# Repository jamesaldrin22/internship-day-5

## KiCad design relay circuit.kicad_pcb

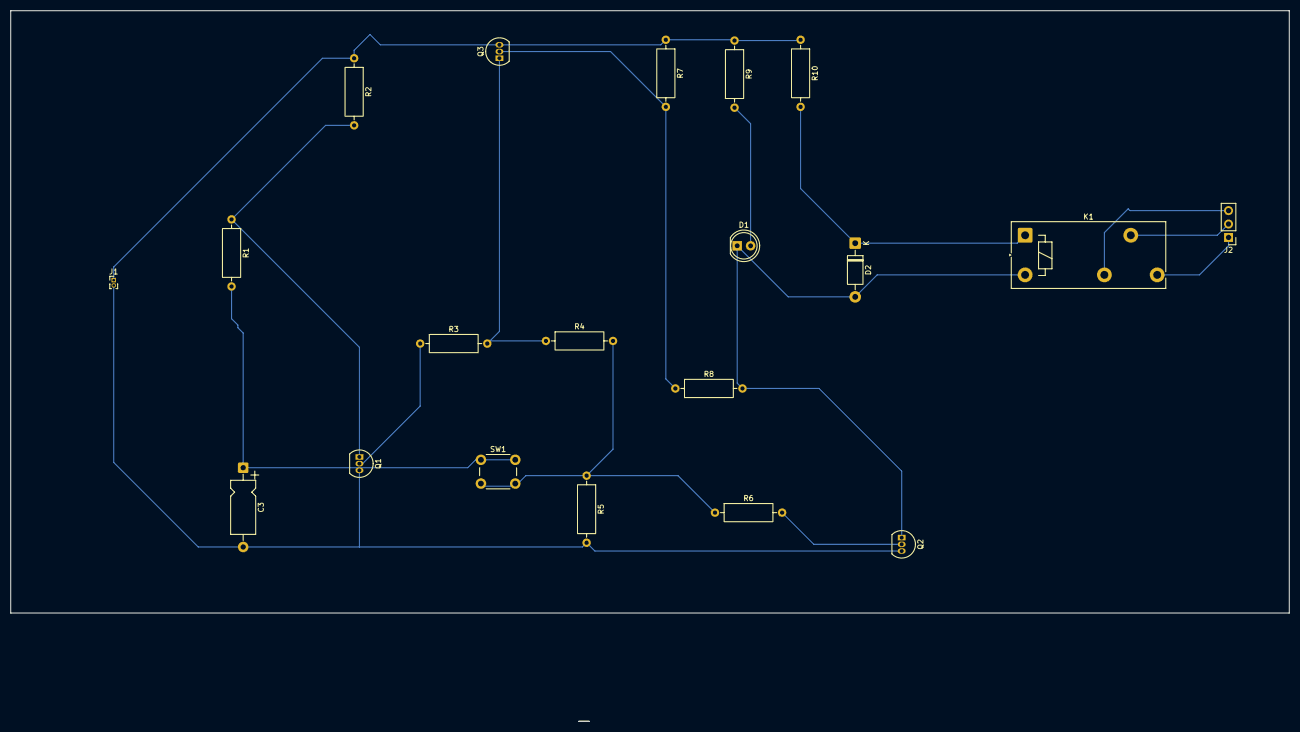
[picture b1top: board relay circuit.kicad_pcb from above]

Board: 2 copper layers, 242.0 x 114.0 mm, 20 parts (0 on the bottom side), 15 nets.

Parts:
C3: C_Polarized_US; CP_Axial_L10.0mm_D4.5mm_P15.00mm_Horizontal
D1: LED; LED_D5.0mm
D2: 1N4007; D_DO-41_SOD81_P10.16mm_Horizontal
J1: Conn_01x02_Pin; PinHeader_1x02_P1.00mm_Vertical
J2: Conn_01x03_Pin; PinHeader_1x03_P2.54mm_Vertical
K1: Fujitsu_FTR-LYCA005x; Relay_SPDT_Finder_40.51
Q1, Q2: BC547; TO-92_Inline
Q3: BC557; TO-92_Inline
R1, R2, R3, R4, R5, R6, R7, R8, R9, R10: R; R_Axial_DIN0309_L9.0mm_D3.2mm_P12.70mm_Horizontal
SW1: SW_Push; SW_PUSH_6mm

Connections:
GND: C3.2, J1.2, Q1.3 (E), Q2.3 (E), R5.2
unnamed: C3.1, R1.2, SW1.1
unnamed: D1.2 (A), R9.2
unnamed: D1.1 (K), D2.2 (A), K1.A2, Q2.1 (C), R8.2
unnamed: D2.1 (K), K1.A1, R10.2
unnamed: J2.1, K1.14
unnamed: J2.2, K1.11
unnamed: J2.3, K1.12
unnamed: Q1.2 (B), R3.1
unnamed: Q1.1 (C), R1.1, R2.2
unnamed: Q2.2 (B), R6.2
unnamed: Q3.2 (B), R7.2, R8.1
unnamed: Q3.1 (C), R3.2, R4.1
unnamed: R4.2, R5.1, R6.1, SW1.2
VCC: J1.1, Q3.3 (E), R2.1, R7.1, R9.1, R10.1

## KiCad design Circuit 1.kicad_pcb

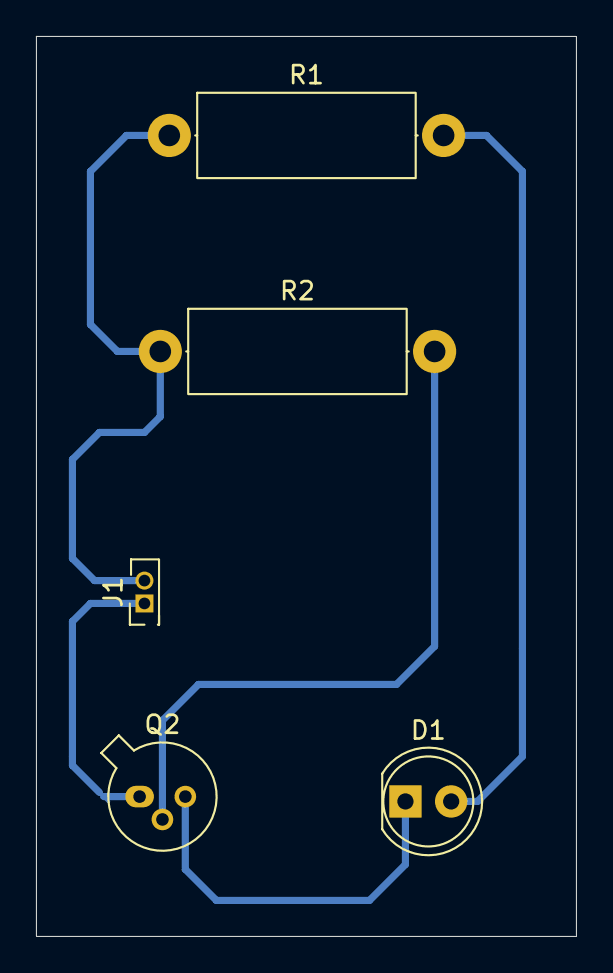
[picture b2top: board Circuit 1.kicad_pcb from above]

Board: 2 copper layers, 30.0 x 50.0 mm, 5 parts (0 on the bottom side), 5 nets.

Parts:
D1: LED; LED_D5.0mm
J1: Conn_01x02_Pin; PinHeader_2x01_P1.27mm_Vertical
Q2: BC108; TO-18-3
R1, R2: R; R_Axial_DIN0414_L11.9mm_D4.5mm_P15.24mm_Horizontal

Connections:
GND: J1.1, Q2.1 (E)
unnamed: D1.2 (A), R1.2
unnamed: D1.1 (K), Q2.3 (C)
unnamed: Q2.2 (B), R2.2
VCC: J1.2, R1.1, R2.1
